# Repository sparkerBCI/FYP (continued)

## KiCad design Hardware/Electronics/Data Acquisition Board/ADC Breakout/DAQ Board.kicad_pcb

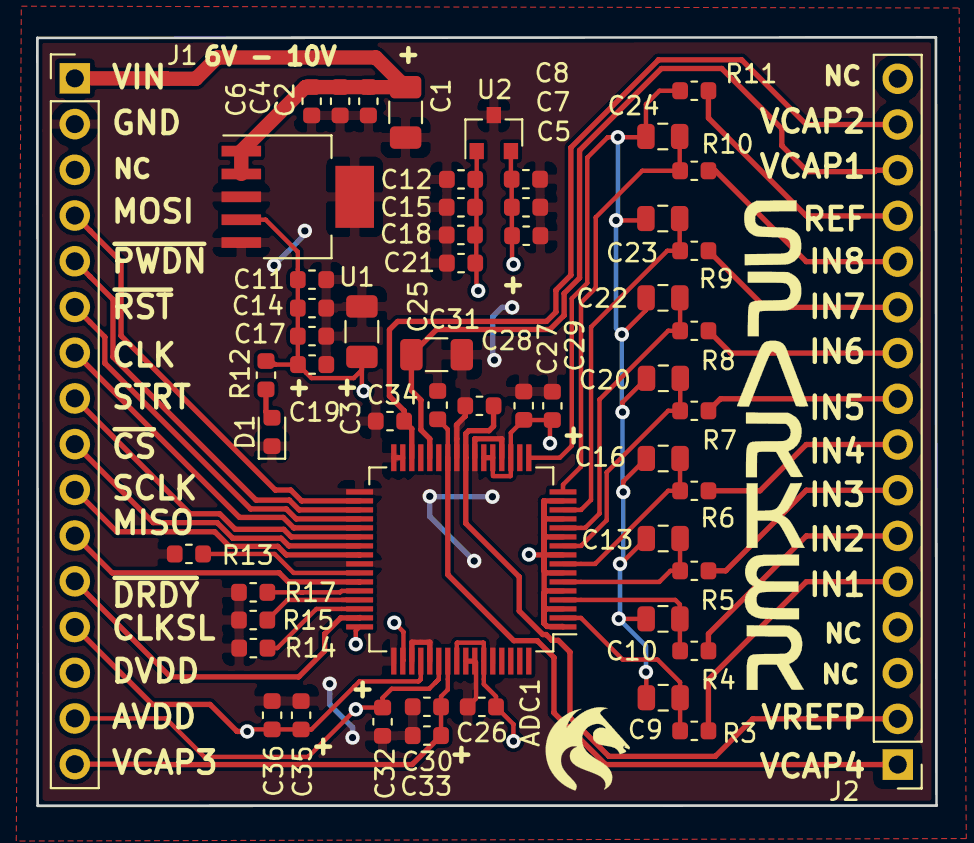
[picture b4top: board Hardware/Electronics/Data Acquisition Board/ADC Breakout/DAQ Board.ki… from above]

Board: 2 copper layers, 50.0 x 42.7 mm, 56 parts (0 on the bottom side), 41 nets.

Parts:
ADC1: ADS1299-8; TQFP-64_10x10mm_P0.5mm
C1, C3, C31: 100uF; C_1206_3216Metric
C2, C5, C19, C21: 10uF; C_0603_1608Metric
C4, C7, C17, C18: 100nF; C_0603_1608Metric
C6, C8, C14, C15: 10nF; C_0603_1608Metric
C9, C10, C13, C16, C20, C22, C23, C24: 24nF; C_0805_2012Metric
C11, C12: 1nF; C_0603_1608Metric
C25, C26, C29, C32, C33, C34, C36: 1uF; C_0603_1608Metric
C27, C30, C35: 0.1uF; C_0603_1608Metric
C28: 10u; C_0603_1608Metric
D1: LTST-C194TBKT; LED_0603_1608Metric
J1, J2: Conn_01x16; PinHeader_1x16_P2.54mm_Vertical
R3, R4, R5, R6, R7, R8, R9, R10, R11: 220k; R_0603_1608Metric
R12: 100; R_0603_1608Metric
R13, R14, R15, R17: 33k; R_0603_1608Metric
U1: MCP1755T-5002E_SOT223-5; SOT-223-6
U2: LM3480-3.3; SOT-23

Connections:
/AVDD: ADC1.1, ADC1.3, ADC1.5, ADC1.7, ADC1.9, ADC1.11, ADC1.13, ADC1.15, ADC1.19, ADC1.21, ADC1.22, ADC1.54, ADC1.56, ADC1.59, C3.1, C5.1, C7.1, C8.1, C11.1, C14.1, C17.1, C19.1, C26.1, C27.2, C29.2, C32.2, J1.15, R12.2, U1.4, U2.2
/AVSS: ADC1.20, ADC1.23, ADC1.25, ADC1.31, ADC1.32, ADC1.33, ADC1.41, ADC1.49, ADC1.51, ADC1.53, ADC1.57, ADC1.58, ADC1.60, C1.2, C2.2, C3.2, C4.2, C5.2, C6.2, C7.2, C8.2, C11.2, C12.2, C14.2, C15.2, C17.2, C18.2, C19.2, C21.2, C25.2, C26.2, C27.1, C28.1, C29.1, C30.1, C31.2, C32.1, C33.1, C34.2, C35.2, C36.2, D1.1, J1.2, R13.2, R14.1, R15.1, R17.1, U1.3, U1.5, U1.6, U2.3
/CLK: ADC1.37, J1.7
/DVDD: ADC1.48, ADC1.50, ADC1.52, C12.1, C15.1, C18.1, C21.1, C35.1, C36.1, J1.13, J1.14, U2.1
/IN1: J2.5, R3.2
/IN2: J2.6, R4.2
/IN3: J2.7, R5.2
/IN4: J2.8, R6.2
/IN5: J2.9, R7.2
/IN6: J2.10, R8.2
/IN7: J2.11, R9.2
/IN8: J2.12, R10.2
/MISO: ADC1.43, J1.11
/MOSI: ADC1.34, J1.4
/REF: J2.13, R11.2
/SCLK: ADC1.40, J1.10
/START: ADC1.38, J1.8
/VCAP1: ADC1.28, C31.1, J2.14
/VCAP2: ADC1.30, C34.1, J2.15
/VCAP3: ADC1.55, C30.2, C33.2, J1.16
/VCAP4: ADC1.26, C25.1, J2.1
/VIN: C1.1, C2.1, C4.1, C6.1, J1.1, U1.1, U1.2
/VREFP: ADC1.24, C28.2, J2.2
/~CS: ADC1.39, J1.9
/~DRDY: ADC1.47, J1.12
/~PWDN: ADC1.35, J1.5
/~RESET: ADC1.36, J1.6
unnamed: ADC1.2, C9.1, R3.1
unnamed: ADC1.4, C10.1, R4.1
unnamed: ADC1.6, C13.1, R5.1
unnamed: ADC1.8, C16.1, R6.1
unnamed: ADC1.10, C20.1, R7.1
unnamed: ADC1.12, C22.1, R8.1
unnamed: ADC1.14, C23.1, R9.1
unnamed: ADC1.16, C24.1, R10.1
unnamed: ADC1.17, C9.2, C10.2, C13.2, C16.2, C20.2, C22.2, C23.2, C24.2, R11.1
unnamed: ADC1.42, R13.1
unnamed: ADC1.44, R17.2
unnamed: ADC1.45, R15.2
unnamed: ADC1.46, R14.2
unnamed: D1.2, R12.1

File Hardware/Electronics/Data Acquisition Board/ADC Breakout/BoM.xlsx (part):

| Ref | Value | Package | Price | SMD | THT | Notes | Digikey Part # | URL | In Box
 | ADC1 | ADS1299-8 | Package_QFP:TQFP-64_10x10mm_P0.5mm | 0 | 1 | 0 | DNP | - | -
 | C1 | 100uF | Capacitor_SMD:C_1206_3216Metric | 3.95 | 1 | 0 | 100µF Molded Tantalum Capacitors 10V 1206 (3216 Metric) 2.5Ohm | 478-6249-1-ND | https://www.digikey.com.au/product-detail/en/avx-corporation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
 | C2 | 10uF | Capacitor_SMD:C_0603_1608Metric | 0.28000000000000003 | 1 | 0 | 10µF ±10% 10V Ceramic Capacitor X5R 0603 (1608 Metric) | 490-10474-1-ND | https://www.digikey.com.au/product-detail/en/murata-electron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
 | C3 | 100uF | Capacitor_SMD:C_1206_3216Metric | 3.95 | 1 | 0 | 100µF Molded Tantalum Capacitors 10V 1206 (3216 Metric) 2.5Ohm | 478-6249-1-ND | https://www.digikey.com.au/product-detail/en/avx-corporation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
 | C4 | 0.1uF | Capacitor_SMD:C_0603_1608Metric | 0.16 | 1 | 0 | 0.1µF ±5% 50V Ceramic Capacitor X7R 0603 (1608 Metric) | 1276-1033-1-ND | https://www.digikey.com.au/product-detail/en/samsung-electro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
 | C5 | 10uF | Capacitor_SMD:C_0603_1608Metric | 0.28000000000000003 | 1 | 0 | 10µF ±10% 10V Ceramic Capacitor X5R 0603 (1608 Metric) | 490-10474-1-ND | https://www.digikey.com.au/product-detail/en/murata-electron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
 | C6 | 10nF | Capacitor_SMD:C_0603_1608Metric | 0.16 | 1 | 0 | 10000pF ±10% 50V Ceramic Capacitor X7R 0603 (1608 Metric) | 445-5662-1-ND | https://www.digikey.com.au/product-detail/en/tdk-corporation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
 | C7 | 0.1uF | Capacitor_SMD:C_0603_1608Metric | 0.16 | 1 | 0 | 0.1µF ±5% 50V Ceramic Capacitor X7R 0603 (1608 Metric) | 1276-1033-1-ND | https://www.digikey.com.au/product-detail/en/samsung-electro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
 | C8 | 10nF | Capacitor_SMD:C_0603_1608Metric | 0.16 | 1 | 0 | 10000pF ±10% 50V Ceramic Capacitor X7R 0603 (1608 Metric) | 445-5662-1-ND | https://www.digikey.com.au/product-detail/en/tdk-corporation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
 | C9 | 24nF | Capacitor_SMD:C_0805_2012Metric | 0.77 | 1 | 0 | 0.022µF ±5% 50V Ceramic Capacitor C0G, NP0 0805 (2012 Metric) | 490-1644-1-ND | https://www.digikey.com.au/product-detail/en/murata-electron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
 | C10 | 24nF | Capacitor_SMD:C_0805_2012Metric | 0.77 | 1 | 0 | 0.022µF ±5% 50V Ceramic Capacitor C0G, NP0 0805 (2012 Metric) | 490-1644-1-ND | https://www.digikey.com.au/product-detail/en/murata-electron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
 | C11 | 1nF | Capacitor_SMD:C_0603_1608Metric | 0.16 | 1 | 0 | 1000pF ±10% 50V Ceramic Capacitor X7R 0603 (1608 Metric) | 311-1080-1-ND | https://www.digikey.com.au/product-detail/en/yageo/CC0603KRX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
 | C12 | 1nF | Capacitor_SMD:C_0603_1608Metric | 0.16 | 1 | 0 | 1000pF ±10% 50V Ceramic Capacitor X7R 0603 (1608 Metric) | 311-1080-1-ND | https://www.digikey.com.au/product-detail/en/yageo/CC0603KRX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
 | C13 | 24nF | Capacitor_SMD:C_0805_2012Metric | 0.77 | 1 | 0 | 0.022µF ±5% 50V Ceramic Capacitor C0G, NP0 0805 (2012 Metric) | 490-1644-1-ND | https://www.digikey.com.au/product-detail/en/murata-electron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
 | C14 | 10nF | Capacitor_SMD:C_0603_1608Metric | 0.16 | 1 | 0 | 10000pF ±10% 50V Ceramic Capacitor X7R 0603 (1608 Metric) | 445-5662-1-ND | https://www.digikey.com.au/product-detail/en/tdk-corporation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
 | C15 | 10nF | Capacitor_SMD:C_0603_1608Metric | 0.16 | 1 | 0 | 10000pF ±10% 50V Ceramic Capacitor X7R 0603 (1608 Metric) | 445-5662-1-ND | https://www.digikey.com.au/product-detail/en/tdk-corporation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
 | C16 | 24nF | Capacitor_SMD:C_0805_2012Metric | 0.77 | 1 | 0 | 0.022µF ±5% 50V Ceramic Capacitor C0G, NP0 0805 (2012 Metric) | 490-1644-1-ND | https://www.digikey.com.au/product-detail/en/murata-electron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
 | C17 | 0.1uF | Capacitor_SMD:C_0603_1608Metric | 0.16 | 1 | 0 | 0.1µF ±5% 50V Ceramic Capacitor X7R 0603 (1608 Metric) | 1276-1033-1-ND | https://www.digikey.com.au/product-detail/en/samsung-electro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
 | C18 | 0.1uF | Capacitor_SMD:C_0603_1608Metric | 0.16 | 1 | 0 | 0.1µF ±5% 50V Ceramic Capacitor X7R 0603 (1608 Metric) | 1276-1033-1-ND | https://www.digikey.com.au/product-detail/en/samsung-electro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
 | C19 | 10uF | Capacitor_SMD:C_0603_1608Metric | 0.28000000000000003 | 1 | 0 | 10µF ±10% 10V Ceramic Capacitor X5R 0603 (1608 Metric) | 490-10474-1-ND | https://www.digikey.com.au/product-detail/en/murata-electron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
 | C20 | 24nF | Capacitor_SMD:C_0805_2012Metric | 0.77 | 1 | 0 | 0.022µF ±5% 50V Ceramic Capacitor C0G, NP0 0805 (2012 Metric) | 490-1644-1-ND | https://www.digikey.com.au/product-detail/en/murata-electron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
 | C21 | 10uF | Capacitor_SMD:C_0603_1608Metric | 0.28000000000000003 | 1 | 0 | 10µF ±10% 10V Ceramic Capacitor X5R 0603 (1608 Metric) | 490-10474-1-ND | https://www.digikey.com.au/product-detail/en/murata-electron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
 | C22 | 24nF | Capacitor_SMD:C_0805_2012Metric | 0.77 | 1 | 0 | 0.022µF ±5% 50V Ceramic Capacitor C0G, NP0 0805 (2012 Metric) | 490-1644-1-ND | https://www.digikey.com.au/product-detail/en/murata-electron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
 | C23 | 24nF | Capacitor_SMD:C_0805_2012Metric | 0.77 | 1 | 0 | 0.022µF ±5% 50V Ceramic Capacitor C0G, NP0 0805 (2012 Metric) | 490-1644-1-ND | https://www.digikey.com.au/product-detail/en/murata-electron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
 | C24 | 24nF | Capacitor_SMD:C_0805_2012Metric | 0.77 | 1 | 0 | 0.022µF ±5% 50V Ceramic Capacitor C0G, NP0 0805 (2012 Metric) | 490-1644-1-ND | https://www.digikey.com.au/product-detail/en/murata-electron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
 | C25 | 1uF | Capacitor_SMD:C_0603_1608Metric | 0.16 | 1 | 0 | 1µF ±20% 16V Ceramic Capacitor X7R 0603 (1608 Metric) | 1276-6524-1-ND | https://www.digikey.com.au/product-detail/en/samsung-electro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
 | C26 | 1uF | Capacitor_SMD:C_0603_1608Metric | 0.16 | 1 | 0 | 1µF ±20% 16V Ceramic Capacitor X7R 0603 (1608 Metric) | 1276-6524-1-ND | https://www.digikey.com.au/product-detail/en/samsung-electro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
 | C27 | 0.1uF | Capacitor_SMD:C_0603_1608Metric | 0.16 | 1 | 0 | 0.1µF ±5% 50V Ceramic Capacitor X7R 0603 (1608 Metric) | 1276-1033-1-ND | https://www.digikey.com.au/product-detail/en/samsung-electro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
 | C28 | 10u | Capacitor_SMD:C_0603_1608Metric | 0.28000000000000003 | 1 | 0 | 10µF ±10% 10V Ceramic Capacitor X5R 0603 (1608 Metric) | 490-10474-1-ND | https://www.digikey.com.au/product-detail/en/murata-electron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
 | C29 | 1uF | Capacitor_SMD:C_0603_1608Metric | 0.16 | 1 | 0 | 1µF ±20% 16V Ceramic Capacitor X7R 0603 (1608 Metric) | 1276-6524-1-ND | https://www.digikey.com.au/product-detail/en/samsung-electro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
 | C30 | 0.1uF | Capacitor_SMD:C_0603_1608Metric | 0.16 | 1 | 0 | 0.1µF ±5% 50V Ceramic Capacitor X7R 0603 (1608 Metric) | 1276-1033-1-ND | https://www.digikey.com.au/product-detail/en/samsung-electro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
 | C31 | 100uF | Capacitor_SMD:C_1206_3216Metric | 3.95 | 1 | 0 | 100µF Molded Tantalum Capacitors 10V 1206 (3216 Metric) 2.5Ohm | 478-6249-1-ND | https://www.digikey.com.au/product-detail/en/avx-corporation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
 | C32 | 1uF | Capacitor_SMD:C_0603_1608Metric | 0.16 | 1 | 0 | 1µF ±20% 16V Ceramic Capacitor X7R 0603 (1608 Metric) | 1276-6524-1-ND | https://www.digikey.com.au/product-detail/en/samsung-electro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
 | C33 | 1uF | Capacitor_SMD:C_0603_1608Metric | 0.16 | 1 | 0 | 1µF ±20% 16V Ceramic Capacitor X7R 0603 (1608 Metric) | 1276-6524-1-ND | https://www.digikey.com.au/product-detail/en/samsung-electro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
 | C34 | 1uF | Capacitor_SMD:C_0603_1608Metric | 0.16 | 1 | 0 | 1µF ±20% 16V Ceramic Capacitor X7R 0603 (1608 Metric) | 1276-6524-1-ND | https://www.digikey.com.au/product-detail/en/samsung-electro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
 | C35 | 0.1uF | Capacitor_SMD:C_0603_1608Metric | 0.16 | 1 | 0 | 0.1µF ±5% 50V Ceramic Capacitor X7R 0603 (1608 Metric) | 1276-1033-1-ND | https://www.digikey.com.au/product-detail/en/samsung-electro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
 | C36 | 1uF | Capacitor_SMD:C_0603_1608Metric | 0.16 | 1 | 0 | 1µF ±20% 16V Ceramic Capacitor X7R 0603 (1608 Metric) | 1276-6524-1-ND | https://www.digikey.com.au/product-detail/en/samsung-electro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
 | D1 | LTST-C194TBKT | LED_SMD:LED_0603_1608Metric | 0.66 | 1 | 0 | Blue 468nm LED Indication - Discrete 3.3V 0603 (1608 Metric) | 160-1837-1-ND | https://www.digikey.com.au/product-detail/en/lite-on-inc/LTS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
 | J1 | Conn_01x16 | Connector_PinHeader_2.54mm:PinHeader_1x16_P2.54mm_Vertical | 1.72 | 0 | 1 | Connector Header Through Hole 16 position 0.100" (2.54mm) | SAM12362-ND | https://www.digikey.com.au/product-detail/en/TSW-116-10-T-S/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

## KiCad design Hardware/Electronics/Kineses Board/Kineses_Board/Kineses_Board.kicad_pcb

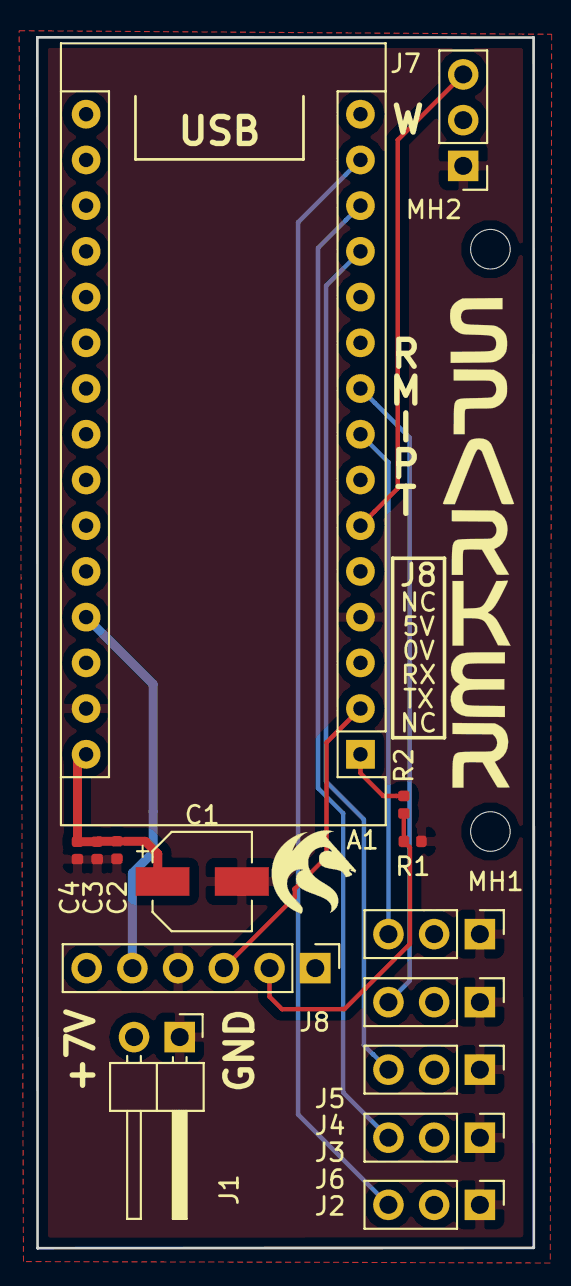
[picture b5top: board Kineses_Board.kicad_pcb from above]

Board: 2 copper layers, 27.6 x 67.3 mm, 19 parts (0 on the bottom side), 12 nets.

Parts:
A1: Arduino_Nano_v3.x; Arduino_Nano
C1: 100u; CP_Elec_5x5.3
C2: 10u; C_0402_1005Metric
C3: 100n; C_0402_1005Metric
C4: 10n; C_0402_1005Metric
J1: Power; PinHeader_1x02_P2.54mm_Horizontal
J2: Thumb; PinHeader_1x03_P2.54mm_Vertical
J3: Index; PinHeader_1x03_P2.54mm_Vertical
J4: Middle; PinHeader_1x03_P2.54mm_Vertical
J5: Ring; PinHeader_1x03_P2.54mm_Vertical
J6: Pinky; PinHeader_1x03_P2.54mm_Vertical
J7: Wrist; PinHeader_1x03_P2.54mm_Vertical
J8: HC-05; PinHeader_1x06_P2.54mm_Vertical
LOGO1: SparkerLogo; NASA_Vertical
LOGO2: UoNLogo; UoN_Small
MH1, MH2: MountingHole; MountingHole_2.2mm_M2
R1: 2K; R_0402_1005Metric
R2: 1K; R_0402_1005Metric

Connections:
/+5V: A1.27, J8.5
/GND: A1.4, A1.29, C1.2, C2.1, C3.1, C4.1, J1.1, J2.1, J3.1, J4.1, J5.1, J6.1, J7.1, J8.4, R1.2
/Index: A1.12, J3.3
/Middle: A1.9, J4.3
/Pinky: A1.13, J6.3
/RX: A1.2, J8.3
/Ring: A1.8, J5.3
/TX: J8.2, R1.1, R2.1
/Thumb: A1.14, J2.3
/VIN: A1.30, C1.1, C2.2, C3.2, C4.2, J1.2, J2.2, J3.2, J4.2, J5.2, J6.2, J7.2
/Wrist: A1.6, J7.3
unnamed: A1.1, R2.2

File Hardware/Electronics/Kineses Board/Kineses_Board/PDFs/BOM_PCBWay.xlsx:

|  |  | xxxx xxxx xxxxx 1PCS BOM (Sample Bill of Materials)
Item # | *Ref Des | *Qty | Manufacturer | *Mfg Part # | Description / Value | *Package | Type | Your Instructions / Notes
1 | A1 | 1 | Arduino | Arduino Nano | Microcontroller | Nonstandard | THT | DO NOT PLACE, DO NOT SUPPLY
2 | C1 | 1 | Panasonic Electronic Components | EEE-1AA101WR | 100µF 10V Aluminum Electrolytic Capacitors Radial, Can - SMD 1000 Hrs @ 85°C | Radial, Can - SMD | SMD
3 | C2 | 1 | Samsung Electro-Mechanics | CL05A106MP8NUB8 | 10µF ±20% 10V Ceramic Capacitor X5R 0402 (1005 Metric) | 0402 | SMD
4 | C3 | 1 | Samsung Electro-Mechanics | CL05F104ZO5NNNC | 0.1µF -20%, +80% 16V Ceramic Capacitor Y5V (F) 0402 (1005 Metric) | 0402 | SMD
5 | C4 | 1 | Yageo | CC0402KRX7R7BB103 | 10000pF ±10% 16V Ceramic Capacitor X7R 0402 (1005 Metric) | 0402 | SMD
6 | J1 | 1 | Adam Tech | PH1RB-02-UA | Connector Header Through Hole, Right Angle 2 position 0.100" (2.54mm) | - | THT | Any manufacturer is OK
7 | J2, J3, J4, J5, J6, J7 | 6 | Amphenol ICC (FCI) | 68000-203HLF | Connector Header Through Hole 3 position 0.100" (2.54mm) | - | THT | Any manufacturer is OK
13 | J8 | 1 | Amphenol ICC (FCI) | 68000-406HLF | Connector Header Through Hole 6 position 0.100" (2.54mm) | - | THT | DO NOT PLACE
14 | LOGO1, LOGO2 | 1 | - | - | Silkscreen Logo | - | - | Silkscreen
15 | MH1, MH2 | 1 | - | - | Mounting Hole | - | THT
16 | R1 | 1 | Yageo | RT0402BRD072KL | 2 kOhms ±0.1% 0.063W, 1/16W Chip Resistor 0402 (1005 Metric) Thin Film | 0402 | SMD
17 | R2 | 1 | Yageo | RT0402FRE071KL | 1 kOhms ±1% 0.063W, 1/16W Chip Resistor 0402 (1005 Metric) Thin Film | 0402 | SMD

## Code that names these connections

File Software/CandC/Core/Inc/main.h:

/* USER CODE BEGIN Header */
/**
  ******************************************************************************
  * @file           : main.h
  * @brief          : Header for main.c file.
  *                   This file contains the common defines of the application.
  ******************************************************************************
  * @attention
  *
  * <h2><center>&copy; Copyright (c) 2020 STMicroelectronics.
  * All rights reserved.</center></h2>
  *
  * This software component is licensed by ST under BSD 3-Clause license,
  * the "License"; You may not use this file except in compliance with the
  * License. You may obtain a copy of the License at:
  *                        opensource.org/licenses/BSD-3-Clause
  *
  ******************************************************************************
  */
/* USER CODE END Header */

/* Define to prevent recursive inclusion -------------------------------------*/
#ifndef __MAIN_H
#define __MAIN_H

#ifdef __cplusplus
extern "C" {
#endif

/* Includes ------------------------------------------------------------------*/
#include "stm32f4xx_hal.h"

/* Private includes ----------------------------------------------------------*/
/* USER CODE BEGIN Includes */

/* USER CODE END Includes */

/* Exported types ------------------------------------------------------------*/
/* USER CODE BEGIN ET */

/* USER CODE END ET */

/* Exported constants --------------------------------------------------------*/
/* USER CODE BEGIN EC */

/* USER CODE END EC */

/* Exported macro ------------------------------------------------------------*/
/* USER CODE BEGIN EM */

/* USER CODE END EM */

void HAL_TIM_MspPostInit(TIM_HandleTypeDef *htim);

/* Exported functions prototypes ---------------------------------------------*/
void Error_Handler(void);

/* USER CODE BEGIN EFP */

/* USER CODE END EFP */

/* Private defines -----------------------------------------------------------*/
#define Ring_AD_Pin GPIO_PIN_0
#define Ring_AD_GPIO_Port GPIOC
#define Middle_ADC_Pin GPIO_PIN_1
#define Middle_ADC_GPIO_Port GPIOC
#define Index_ADC_Pin GPIO_PIN_2
#define Index_ADC_GPIO_Port GPIOC
#define Thumb_ADC_Pin GPIO_PIN_3
#define Thumb_ADC_GPIO_Port GPIOC
#define VSUPPLY_ADC_Pin GPIO_PIN_0
#define VSUPPLY_ADC_GPIO_Port GPIOA
#define Thumb_Pin GPIO_PIN_6
#define Thumb_GPIO_Port GPIOA
#define Index_Pin GPIO_PIN_7
#define Index_GPIO_Port GPIOA
#define Pinky_ADC_Pin GPIO_PIN_4
#define Pinky_ADC_GPIO_Port GPIOC
#define Wrist_ADC_Pin GPIO_PIN_5
#define Wrist_ADC_GPIO_Port GPIOC
#define Middle_Pin GPIO_PIN_0
#define Middle_GPIO_Port GPIOB
#define Ring_Pin GPIO_PIN_1
#define Ring_GPIO_Port GPIOB
#define Pinky_Pin GPIO_PIN_12
#define Pinky_GPIO_Port GPIOD
#define Wrist_Pin GPIO_PIN_13
#define Wrist_GPIO_Port GPIOD
/* USER CODE BEGIN Private defines */

/* USER CODE END Private defines */

#ifdef __cplusplus
}
#endif

#endif /* __MAIN_H */

/************************ (C) COPYRIGHT STMicroelectronics *****END OF FILE****/

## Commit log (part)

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2019-08-09 Removed Readme
2019-08-09 Cover page 90%, added headings for forematter
2019-08-18 Started literature review for feature extraction
2019-08-19 updated some project settings
2019-08-19 Started signal acquisition section
2019-08-22 Initial commit of DAQ board. Unversioned a settings file from pwm_with_serial/.settings
2019-08-27 Finished AAR additions
2019-08-27 reader now checks accuracy of 6 classification techniques, initial commit of Classification Technique Comparison.docx
2019-08-28 Data labels now correct, more accurate times
2019-09-15 Fixed windowing and FFT N-point issue in reader.m (might now be new_reader.m?). Initial commit of Kaushik's code. Added Hanning and Gaussian windows. Added heatmap_maker.m. Highest accuracy is now 65%
2019-09-16 Added a little more about EEGs
2019-09-17 Removed readme.txt and modified new_reader.m
2019-09-17 Added Arduino Nano and associated datasheets
2019-09-25 Initial commit. Accuracy around 80%
2019-10-01 Fixed quote marks in dct_reader.m. Added missing datasets
2019-10-13 DAQ board laid out, need to start routing
2019-10-14 Bio background improved, added DCT stuff
2019-10-14 Finished DCT
2019-10-15 Started converting to word references
2019-10-15 Small changes
2019-10-16 Referencing converted to EndNote
2019-10-20 Kineses Board layout finished, about to start routing
2019-10-20 Routing finished
2019-10-20 Routed new LDOs
2019-10-22 Updated pics, added more to hardware section
2019-10-23 Initial commit of gerber files
2019-10-28 Updated gerbers. Initial commit of interim Presentation
2019-10-29 updates to report
2019-11-02 Added a couple thousand words to the report
2019-11-04 Lots of additions to report
2019-11-05 Report just about done
2019-11-05 Initial commit of Interim Report - A Brain Computer Interface Controlled 3D Printed Prosthetic - Samuel Parker and Kaushik Mahata.docx, Gantt Chart.xlsx, and several photos
2019-11-07 Added results
2019-11-08 Interim Report ready for submission
2019-11-09 Initial Commit of Photos
2019-11-25 Added check for angle range
2019-11-30 Finished Presentation
2019-12-19 Modified some caps, probably due to a voltage level incompatibility
2019-12-22 X Macro setup of Register Table
2019-12-27 small code cleanup
2019-12-27 added uncrustify comments
2019-12-27 created batch file to run Uncrustify
2019-12-27 fixed problem where RESET from FTDI chip was connected via cap to GND not RESET. Added 10u cap across reset PB.
2019-12-27 Added 100k resistor
2019-12-27 Added pullup to ADS1299 CS pin
2019-12-27 updated PB url
2019-12-27 Created branch for new EEG connector work
2019-12-28 ran DRC
2019-12-28 Generated Output Files
2019-12-28 Removed a stub and moved some vias. Regenerated production docs
2019-12-28 Created Tag to store production save of DAQ board
2019-12-28 removed a few extra vias
2019-12-28 removed some more vias
2019-12-28 Added SWD programming header
2019-12-28 Added 3V3 extra low drop out voltage regulator
2019-12-29 Finished STM32F407VGTx, working on comms
2019-12-29 Finished Schematic
2019-12-29 Added footprints for everything
2019-12-29 made a square section, it's a bit big though
2019-12-29 About to start routing
2019-12-30 Started Routing
2020-01-02 about to grid vias
2020-01-02 Set up SPI interface and started Pin_Map
2020-01-04 Finished BoM
2020-01-04 Removed second sheet
2020-01-04 Created pin array, and uncrustified sources
2020-01-06 Added more getters and setters
2020-01-07 Changed uncrustify config
2020-01-07 Changed tab size to 2 and indent cols to 2
2020-01-07 Even more interface functions
2020-01-08 Found a bug where the setters only look at the set bit case, not the clear bit case. Will fix
2020-01-08 Checked that all value = old_value & 0xXX are "&"s and correct numbers
2020-01-08 Register current value is now updated when read from the device, instead of dead reckoning that nothing changes since device is initialised
2020-01-09 Added doxygen documentation generation
2020-01-09 testing keywords
2020-01-09 Stopped Uncrustify from removing leading spaces in multi-line comments
2020-01-09 Adding doxygen comments
2020-01-10 changed where the comments align
2020-01-13 Uncrustified, and changed doxygen comments. Added dot graphs to doxygen output.
2020-01-15 Actually runs now. Included #defines to enable/disable SPI comms
2020-01-15 Moved #define into ADS1299.h as every file that needs it includes this file
2020-01-16 Fixed a logic error that was allowing corrupt samples to be processed
2020-01-17 All functionality written.
2020-01-18 Added doxygen comments to ADS1299_Params.h Changed uncrustify settings to bring comments a little closer. Ran doxygen.
2020-01-18 Finished doxygen comments, changed some doxygen settings
2020-01-20 Flipped the DC connector
2020-01-20 Small change to schematic
2020-01-20 Added a PARAM_TABLE which holds info about the bytes in the registers. Converted all magic numbers to param array references
2020-01-21 Now have 7 channel ADC and USART working with DMA
2020-01-28 Made sure everything works after merge
2020-01-29 Improved fabrication outputs
2020-01-31 Added a heading to the In Box column
2020-01-31 Changed how comms messages generate the timestamp for a more consistent millisecond reading
2020-02-19 started sample parsing
2020-02-24 Can now parse samples, save to a big array of past samples, collect an epoch, convert from 2s compliment to decimal, convert from decimal to volts, and get the DCT coefficients of the voltage signal
2020-03-01 Fixed out by one error
2020-03-03 Changed the pins to the arduino expected numbers, rather than the numbers they are on the package
2020-03-24 Adding ADC breakout
2020-03-24 Small clearance changes, silkscreen art added
2020-03-24 Removed pullup resistor on /CS. Reran production pdfs and plotted schematic
2020-03-24 Modified production PDFs
2020-03-26 Small routing change, added extra silkscreen labels
2020-03-26 ADC BREAKOUT ASSEMBLY TAG
2020-04-01 DRC passes
2020-04-01 Removed BT / USB switch, changed reset button switch so now it will be correct
2020-04-01 Ran the Gerbers, made fab layer look fab
2020-04-01 Fixed schematic note regarding voltage divider ratio
2020-04-09 Changed clock speed to 168MHz, now parses and allocates 1 sample, added UART3
2020-04-23 Changed hardware to make USB use USART2 to be binary compatible with Dev Board. Moved some components accordingly.
2020-04-23 CLASSIFICATION AND CONTROL BOARD PRODUCTION
2020-05-19 Added decemation check before sending sample. Ran uncrustify and doxygen
2020-05-19 Seems to have imported ok
2020-05-19 Wired up level shifter and made changes to ADS1299 schematic to match breakout board
2020-05-26 Created Readme
2020-05-26 Added arduino script to read external test signal
2020-05-26 Forgot to save
2020-05-27 Small schematic updates, changed test point nets, pcb changes
2020-05-27 Updated BoM and added Block Logos
2020-06-01 Got softwareSerial written in
2020-06-01 Started porting SPI interface
2020-06-01 Uncrustified and fixed check_register
2020-06-01 updated doxygen. Weird bug, main page doesn't work on a fresh run and needs to be reverted to previous version. Not sure what changed, will have to look at Sparker_DAQ.ino history and see.
2020-06-01 Doxygen GUI doesn't work, from now on use CLI
2020-06-01 Copied Sparker DAQ which will be modified to generate SVM Training Data
2020-06-02 Added Sparker DAQ V2
2020-06-02 Added 8 channel data acquisition
2020-06-03 Hardware Updates
2020-06-03 Added a fair bit of hardware info and some references
2020-06-03 Added a few appendixes, small structure change
2020-06-06 Increased line spacing to 1.5
2020-06-06 Now writes samples to serial, for debugging
2020-06-06 Added C&C software info, started talking about modular ADS1299 board
2020-06-06 Added svm training data generator w BT
2020-06-07 Unzip this and commit it
    This calcs the DCT then writes the coeffs * 100 to the UART. Coeffs match with matlab
2020-06-07 Removed zipped archive. Added more education info
2020-06-08 Added a reference
2020-06-10 Added usually empty directory
2020-06-10 Now receives over UART with interrupts
2020-06-10 Can now receive one epoch of data, and convert it to an array of longs
2020-06-10 Can now calculate DCT
2020-06-11 Modified to now not need a CR or LF at the end of each sample
2020-06-11 Added weight vector, bias, and scale outputs from linear svm
2020-06-11 Split ISR into pre- and post-model reception. Added process sample function to simplify ISR
2020-06-11 Moved where the interrupt is re-enabled
2020-06-11 Added second half of the if statement
2020-06-11 Removed a space lol
2020-06-12 Added function to unify parsing of RX buffer
2020-06-12 Changed the SVM to be a pointer, malloc stuff. Haven't tested loading weights yet
2020-06-14 temporarily made daq output over serial for debugging
2020-06-14 New Session
2020-06-14 Added an extra reference, and added some results
2020-06-14 Reasons for discrepancy
2020-06-15 Now gets the weight vector
2020-06-15 Model fully loaded
2020-06-15 Now prints floats, and added DCT calc to report
2020-06-15 Removed unnecessary free because it was causing a hardfault. coeffs was a local variable, no need to free.
2020-06-15 Added a cross reference
2020-06-15 Can now calc dot product. tested against matlab
2020-06-15 Mostly comment changes. Moved a line that was repeated in both branches of if statement
2020-06-15 Comments
2020-06-17 Switched to newline between each sample. Test BT connection and it works
2020-06-17 Can send and calc DCT of sample after getting SVM model
2020-06-17 Outputs predicted class label on serial bus
2020-06-17 ran the classifier
2020-06-17 Added screenshot, removed prints to console
2020-06-17 labels save to array
2020-06-17 Reverted back to printing labels because that worked. Changed SVM to not need a malloc again because it seemed troublesome but it really just needed a powercycle
2020-06-17 Labels are now in an array, and matlab will make sure samples are sent exactly 1s between epochs. Need to update DAQ transmission to make sure there's a second
2020-06-18 Added a photo, and Rick Middleton reference. About to start User Manual Lab Doc
2020-06-18 Hardware setup done
2020-06-18 Updated BoM and took some pics
2020-06-18 Added BoM
2020-06-18 Added CandC Schematic Appendix
2020-06-18 Added C and C gerbers appendix
2020-06-18 Fixed TX<->TX problem, edited a Photo.jpg
2020-06-18 Added references, changed orientation of CandC gerbers appendix
2020-06-18 Updated the data acquisition system schematics appendix
2020-06-18 Modified a reference, created doc for poster
2020-06-18 poster updates
2020-06-18 Bom Updates
2020-06-19 DAQs now send an epoch at a time
2020-06-19 Small report changes, mostly highlighting
2020-06-20 Not sure what this change is...
2020-06-20 Prescaler was set to 1. Set to 480 and works
    PWM frequency 540Hz to Arduino's 490
2020-06-21 Added rest of the PWM channels, project builds
2020-06-21 Started Kaushik's first round of changes
2020-06-21 Added some more changes
2020-06-22 Added a tonne about SVMs
2020-06-22 Kaushik content changes done
2020-06-22 Updated all fields
2020-06-23 references
2020-06-24 Minor edits
2020-06-24 Concs and Recs updated
2020-06-24 Formatting
2020-06-24 List of Concs Done
2020-06-24 Literally just added a space
2020-06-25 Added documentation appendix and modified equation numbers
2020-06-26 First Pass
2020-06-26 Read through, justified headings and references
2020-06-26 Checked spacing, caption locations, equations
2020-06-26 Everything ready to submit
2020-06-28 Pasted in updated main.c
2020-06-28 workspace language settings update
2020-06-28 Fixed flipped logic in main.c
2020-06-29 Modified training generator to send everything over BT, modified DAQ to send 256 samples
2020-06-29 Modified plotter to only need 1 channel, removed prompts and added labels to data
2020-06-30 Changed wording of state of the art, added Kaushik to author list
2020-06-30 Added ADCs
2020-06-30 Added missing drivers
2020-06-30 Fiddled with resistances, etc.
2020-07-01 Added bang bang control, untested, HAL delay hangs
2020-07-01 Lowered Priority of Everything other than systick
2020-07-01 Added some new data, and changed which dataset matlab is looking at
2020-07-01 Added FFT plot for better frequency visualisation
2020-07-01 changed some plots
